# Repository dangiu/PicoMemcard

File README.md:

# PicoMemcard++

PicoMemcard++ lets you build a supercharged PlayStation memory card that can connect to your computer via USB, allowing you to transfer save files directly to and from your PSX. It can also be used to repurpose broken or counterfeit memory cards, turning them into something far more capable using only an RP2040. This project is a fork of the original work by [Dangiu].

When I decided to get involved, the original repository was read-only and no longer actively developed. I had a few simple goals in mind:
* There are many very cheap RP2040-based boards with built-in QSPI flash (up to 16MB), which can hold up to 128 virtual PSX memory card images.
* The project had been split into two versions: PicoMemcard (stuck at version 1.0) and PicoMemcard+ (which depends on a microSD card). I thought it made sense to merge them so both could benefit from ongoing updates.
* That’s when my journey with the project began.

## Features
* Able to faithfully simulate PSX Memory Card
* USB connection to import/export saves
* Allows to copy saves to/from any other memory card (using original PSX file manager)
* Allows to play burned CDs (thanks to [FreePSXBoot])
* Cheaper than an original memory card
* Can store hudreds of memory card images

## PicoMemcard++ vs PicoMemcard+/PicoMemcard
Because some features can’t be implemented using only a Pico/RP2040-Zero and require additional hardware, the original project was split into two versions:

* PicoMemcard was inspired by this project and aims to be the simplest and easiest version to build. It only requires a Raspberry Pi Pico, RP2040-Zero, or RP2040-Pro Micro. The original version supported only a single virtual memory card.
* PicoMemcard+ adds support for extra features, such as multiple memory card images, by using an additional SD card. However, this version also requires extra hardware, specifically a MicroSD SPI expansion board.
* **PicoMemcard++** (this fork) brings some of the features from PicoMemcard+ to the original PicoMemcard design, allowing users to switch between different memory cards without needing additional storage hardware. It’s a lower-cost option that combines ideas from both designs.

This approach was chosen because many users want the cheapest possible solution and don’t care about extra features. Others, however, are willing to spend a bit more to gain additional functionality.

Please note that the current release of PicoMemcard++ (when used without an SD card) comes with some limitations:
* Non-transparent write-back: during the synchronization process used to save new data, the memory card may briefly appear to disconnect.
* The connection to the PC (used to transfer save files from PSX games) is not fully plug-and-play. In some cases, you may need to reconnect the device.

## Bill of materials
* ** RP2040 Pico/Zero/Pro Micro** (around 2-3€).
* One of:
    * Custom [PicoMemcard PCB](#picomemcard-pcb)
    * Broken/Counterfeit/Original PSX Memory Card (counterfeit ones can be found on AliExpress for around 2-3€)
    * PSX/PS2 Controller Cable
    * CAT5 network cable and a bit of creativity.

Basically anything that will allow you to interface with the memory card slot pins will do. If you have a broken contoller you can cut off the cable and use that since controllers and memory cards share the same bus. Of course, plugging your memory card into the controller slot will prevent you from using 2 controllers at the same time.

[This guy] assembled one using a 3d-printed plastic shell and simple CAT5 network cable. I belive this is the cheapest method anybody has come up with until now.

In total building a PicoMemcard wil cost you less than buying a used original Memory Card!

## Video

## DIY

Getting your hands dirty, we will explore two different routes:
    * Custom [PicoMemcard PCB](#picomemcard-pcb)
    * [PSX Memory Card] (#picomemcard++-using-memory-card)

### PicoMemcard PCB

These are the custom PCBs designed and manufactured specifically for this application. They are not strictly required but make it much easier to build PicoMemcard since you don't need to cut up another memory card and all the soldering pads are easily accessible. All you need to do is to solder the Pico/RP2040-Zero on top of the PCB using a soldering iron.

The Raspberry Pi Pico or RP2040-Zero must sit flush on top of the PCB, fortunately both the Pico and RP2040-Zero provide castellated holes that are easy to solder directly to the PCB's pads. You can use some electrical tape to hold the board in place while you solder the first pins.

I've created a new version of the original PCBs the major difference are:
* The general size is smaller
* A new micro SD card module is supported. This module is smaller, easier to solder and should solve some of the power related issues that were previously present
* Is fitted for the installation of phisical switches used to switch memory card when PicoMemcard+ is used in systems that do not support switching via controller input (e.g. all PS2 models).

The KiCad and Gerber files are available in the repository. If you want to support the project you can request a PCB [from here]. 
Keep in mind that with the PS2 support release that will eventually happen the PCB may undergo some additional changes before its design is finalized.

### PicoMemcard++ using Memory Card
Raspberry Pi Pico, Pro Micro or RP2040-Zero require different pin usage for full compatibility.

The wiring diagrams below show how to build PicoMemcard by wiring respectively a Pico and an RP2040-Zero to a counterfeit memory card. For the other cases (wiring directly to the PSX or using a controller cable) the pins on Pico and RP2040-Zero are the same, the pinout of the PSX/controller can be found on [psx-spx]. The images show the bottom side of the memory card with the cover removed.

The dashed line on the PCB of the memory card is where you should cut a groove deep enough to disconnect the original circuitry from the traces. The yellow squares above the line indicate where you should scrape away the protective film in order to expose the copper traces and solder the wires onto them.

Finally the area at the bottom of the memory card is where you can cut a hole to feed the wires through connecting them to the Pico.
If you are using an RP2040-Zero you can also cut away part of the original Memory Card circuitry to fit it inside the original shell.

The connections in the PicoMemcard+ area are optional (using the optional MicroSD expansion board). Also remember to connect both ground and power to your SD card module (see [MicroSD Module](#microsd-module-for-picomemcard) section for more information).

#### PicoMemcard++ using a CounterFeit Memory Card without microSD module

In this subsection, I’ll show how to build a very simple version of the device without using an external microSD card. Since I don’t own a 3D printer, I used a counterfeit PSX memory card shell instead. The process involves the following steps:
1. Buy a memory card and unscrew the case:

2. Extract the PCB and desolder the internal components

3. Solder the RP2040-based board to the PCB

4. Enjoy the final result.

### MicroSD Module
There are many variations of MicroSD expansion boards with different pinouts and interfaces. The only requirement for PicoMemcard++ is that the module must provide an SPI interface. SPI interfaces have at least the following pins:
* Chip Select (CS) (sometime also called Slave Select (SS)).
* Clock (SCK or CLK).
* Master Output Slave Input (MISO).
* Master Input Slave Output (MOSI).

In addition you will need to connect power and ground to your module, some modules are design to work with 5V others with 3.3V (or both), luckily for us both voltages are available on Pico and RP2040-Zero as shown in the schematic in the section [above](#picomemcard-using-memory-card). Some module provides additional pins that can be left disconnected.

The new versions of the PCB are designed to use small modules such as this one:

This is mainly due to the following reasons:
* It comes withouth pre-soldered headers which makes it easier to solder onto the PicoMemcard PCB.
* Its smaller form factor allows for more flexibility.
* It should have less power issue than prevously used modules.

A good source for these modules is Aliexpress, in general you can search for `MicroSD SPI Expansion Board` and buy the cheapest one you find.

## Installation
1. Download the latest [release] for your board (Raspberry Pi Pico and RP2040-Zero require different binaries).
2. While pressing the 'BOOTSEL' or 'BOOT' button on your board, plug it into your computer. 
3. Drag and drop the PicoMemcard release onto your Raspberry Pi Pico.
4. PicoMemcard should appear on your PC as a USB drive.
5. Upload a memory card image to your PicoMemcard.

## Transfering Data
Memory card images must be exactly 128KB (131072 bytes) in size. PicoMemcard++ only supports files with `.MCR` extensions. However, `.MCR` and `.MCD` extensions are interchangable and can be converted to one another simply via renaming.
For other file formats, try using [MemcardRex] for converting to the desired output.

* **PicoMemcard** only supports a single image which must be named exactly `MEMCARD.MCR`.
* **PicoMemcard+** supports hundreds of images. Each image must be named `N.MCR` where `N` is an integer number (e.g. `0.MCR`, `1.MCR`...). On boot your previously loaded image will be reloaded, unless it's a fresh card then `0.MCR` will be loaded.
* **PicoMemcard++** supports up to 10 memory card images. As before, the naming convention is `N.MCR`, where `N` is an integer number (e.g. `0.MCR`, `1.MCR`...). n systems with 16MB of flash memory — such as some boards like the RP2040-Pro Micro — the limit is increased to 100 images.

Inside `docs/images` you can find two memory card images. One has a couple of saves on it so you can test if everything works correctly, the other is completely empty.

## Switching/Creating Images
On **PicoMemcard+** you can switch the active memory card image with the following inputs:
* `L1 + L2 + R1 + R2 + DPAD UP` will switch to the next image (e.g from `1.MCR` to `2.MCR`).
* `L1 + L2 + R1 + R2 + DPAD DOWN` will switch to the previous image (e.g from `1.MCR` to `0.MCR`).

Additionally you can create a new empty memory card image (and automatically switch to it) by pressing  `L1 + L2 + R1 + R2 + TRIANGLE`.

**Attention**: this method only works on PSX if the controller used to provide the input is plugged in the same slot as PicoMemcard (exactly under it). Using a controller from a different slot will have no effect.

Additionally this method does not work on PS2 Memory Cards and Controllers are wired on a different bus.

## Syncing Changes
Generally speaking, new data written to PicoMemcard (e.g. when you save) is permanently stored only after a short period of time (due to hardware limitation). The on board LED indicates whether all changes have been stored or not, in particular:
* On RP2040 Pico/Pro Micro the LED will be on when all changes have been saved, off otherwise.
* On RP2040-Zero the LED will be solid when all changes have been saved, red otherwise.

Unlike **PicoMemcard+** that tries to write new changes as soon as possible, **PicoMemcard++** will generally do it only after a period of inactivity (around 5 seconds).

**Attention**: after you save your game, make sure to wait for the LED to be solid before turning off the console otherwise you might lose your more recent progress!

## 3D-Printed Case
I've finally designed a 3D-printable case for the different PicoMemcard PCBs. It helps inserting correctly the PCB and ensuring that the the connection to the PSX is optimal. The same result, albeit more janky, can be achieved using a folded sheet of paper as a spacer.

The cases are designed following a minimalistic approach, they consist of a single piece which holds tightly the PCB using very small clips without requiring any additional hardware. To assemble it, simply slide in the PCB from the back of the case (opposite to the side connecting to the PSX). Cases for the fullsize PCB are designed to support the MicroSD expansion module.

Here is the download for the STL files:
* [Design by DanGiu](https://www.thingiverse.com/thing:5488778)

If you don't like this case you can check out other designs many people have already created! I've not tested them personally but here they are:
* [Design by brik1111](https://www.thingiverse.com/thing:5453156)
* [Design by bbsan2k](https://www.thingiverse.com/thing:5460187)

## Troubleshooting and LED Indicator
Generally speaking the onboard LED will provide a pretty good indication regarding the status of PicoMemcard.

In particular, the RP2040-Zero has RGB LED that provides a more clear output. The Pico on the other hand as only a green LED and different blinking patterns indicate different statuses.

### PicoMemcard++ Status
| Status | Pico | RP2040-Zero
| --- | --- | --- |
| Failed to read SD card | Blinking led  | Red blinking led
| Data not fully synced (do not turn off PSX)| Led off | Red led (or flashing red) |
| Data synced | Led on | Solid led |
| Memory Card image changed | Three fast blinks | Single blue blink |
| Memory Card image not changed (end of list) | Nine fast blinks | Single orange blink |
| New Memory Card image created | Multiple very fast blinks | Single light blue blink |

## General Warnings
I would recommend to never plug PicoMemcard both into the PC (via USB) and the PSX at the same time! Otherwise the 5V provided by USB would end up on the 3.3V rail of the PSX. I'm not really sure if this could cause actual damage but I would avoid risking it.

If you really need to have the Pico plugged into both the USB and PSX (e.g. for debugging purposes), disconnect the 3.3V line from the VBUS pin. In this way you can power on the Pico using a simple USB phone charger or by plugging it into your PC.

As a disclamer, I don't take any responsability for what will happen to your console when using PicoMemcard/PicoMemcard+.

## Project Updates
### 16 may 2026
A fork of the original project that revives and merges previously abandoned features, along with updated documentation and support for additional boards and functionalities.

### 5 February 2023
Sorry everybody but I've been quite inactive on the project lately. Due to a change of job IRL I have less time to work for the moment.
Anyway, behind the scenes I've been trying to add support for PS2 memory card but I'm afraid that will require the addition of an extra hardware component unless I am able to develop an efficient cacheing mechanisms or something similar. Anyway I'll keep working on it when I have free time. I have in mind many improvement for the project and I think the future of it is going to be exciting.

Special thanks to everybody that supported it so far! You are all amazing.

## Design
For people interested in understanding how PicoMemcard works I provide a more extensive explanation in [this post] (although now somewhat outdated).

## Thanks To
* [psx-spx] and Martin "NO$PSX" Korth - PlayStation Specifications and documented Memory Card protocol and filesystem.
* [Andrew J. McCubbin] - Additional information about Memory Card and Controller communication with PSX.
* [littlefs] - Filesystem designed to work on NOR flash used by many microcontrollers, including the Raspberry Pi Pico.
* [ChaN FatFS] - FAT filesystem implementation for embedded devices.
* [Scoppy] - Use your Raspberry Pi Pico as an oscilloscope, very cheap and accurate. Without this I would have not been able to debug many issues.
* [PulseView] - Used to import, visualize and manipulate the data from Scoppy on a PC.

[Dangiu]: https://github.com/dangiu/PicoMemcard
[FreePSXBoot]: https://github.com/brad-lin/FreePSXBoot
[psx-spx]: https://psx-spx.consoledev.net/pinouts/#controller-ports-and-memory-card-ports
[Andrew J. McCubbin]: http://www.emudocs.org/PlayStation/psxcont/
[littlefs]: https://github.com/littlefs-project/littlefs
[ChaN FatFS]: http://elm-chan.org/fsw/ff/00index_e.html
[Scoppy]: https://github.com/fhdm-dev/scoppy
[PulseView]: https://sigrok.org/wiki/PulseView
[release]: https://github.com/dangiu/PicoMemcard/releases/latest
[this post]: https://dangiu.github.io/2022/05/13/picomemcard.html
[from here]: https://forms.gle/f6XHtz6W5fn5qDZV7
[This guy]: https://github.com/MrSVCD/PicoPSX_3D
[MemcardRex]: https://github.com/ShendoXT/memcardrex

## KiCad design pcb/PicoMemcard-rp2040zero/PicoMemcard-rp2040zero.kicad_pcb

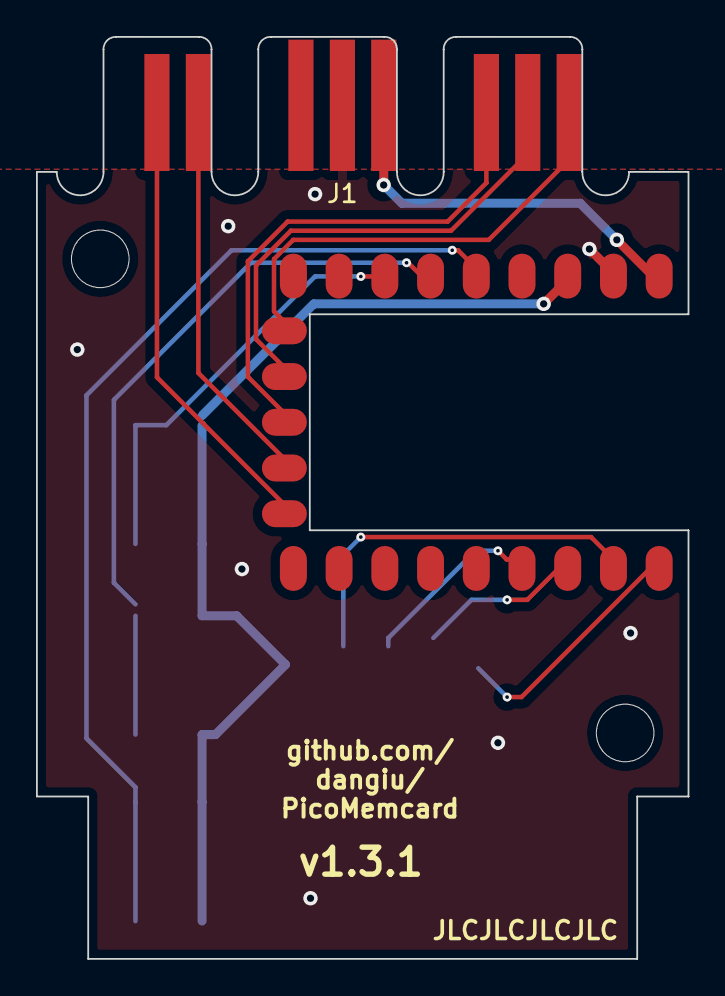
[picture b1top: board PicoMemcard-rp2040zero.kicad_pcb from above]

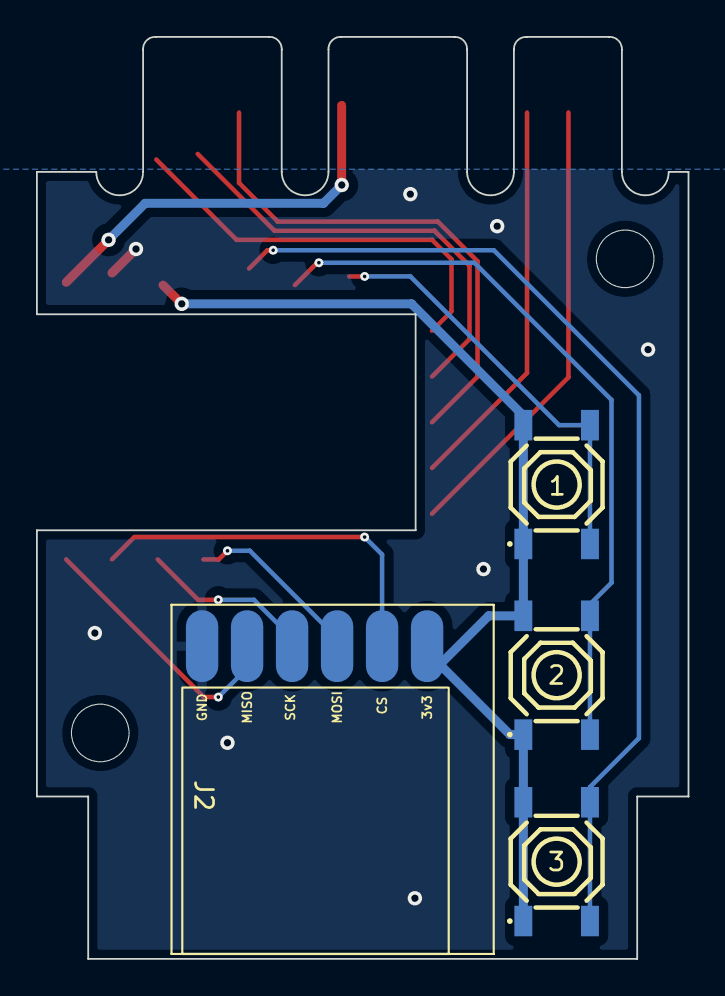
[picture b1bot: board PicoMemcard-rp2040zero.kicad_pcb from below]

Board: 2 copper layers, 36.2 x 51.2 mm, 8 parts (4 on the bottom side), 15 nets.

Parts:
1, 2, 3: TS-1187A-B-A-B; SW-SMD_4P-L5.1-W5.1-P3.70-LS6.5-TL-2
H1, H2: M3; MountingHole_3.2mm_M3
J1: PSX Memory Card Interface; MemoryCardConnector
J2: MicroSD SPI; MicroSD_SPI_small
U1: rp2040-zero; rp2040-zero-smd

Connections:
+3V3: 1.1 (A), 1.2 (B), 2.1 (A), 2.2 (B), 3.1 (A), 3.2 (B), J2.1, U1.21 (3V3)
+5V: J1.5 (5V), U1.23 (5V)
ACK: J1.8 (ACK), U1.14 (13)
CLK: J1.7 (CLK), U1.13 (12)
CMD: J1.2 (CMD), U1.11 (10)
CS: J2.2, U1.2 (1)
DAT: J1.1 (DAT), U1.10 (9)
GND: J1.4 (GND), J2.6, U1.22 (GND)
GP26: 1.3 (C), 1.4 (D), U1.17 (26)
GP27: 2.3 (C), 2.4 (D), U1.18 (27)
GP28: 3.3 (C), 3.4 (D), U1.19 (28)
MISO: J2.5, U1.1 (0)
MOSI: J2.3, U1.4 (3)
SCK: J2.4, U1.3 (2)
SEL: J1.6 (SEL), U1.12 (11)

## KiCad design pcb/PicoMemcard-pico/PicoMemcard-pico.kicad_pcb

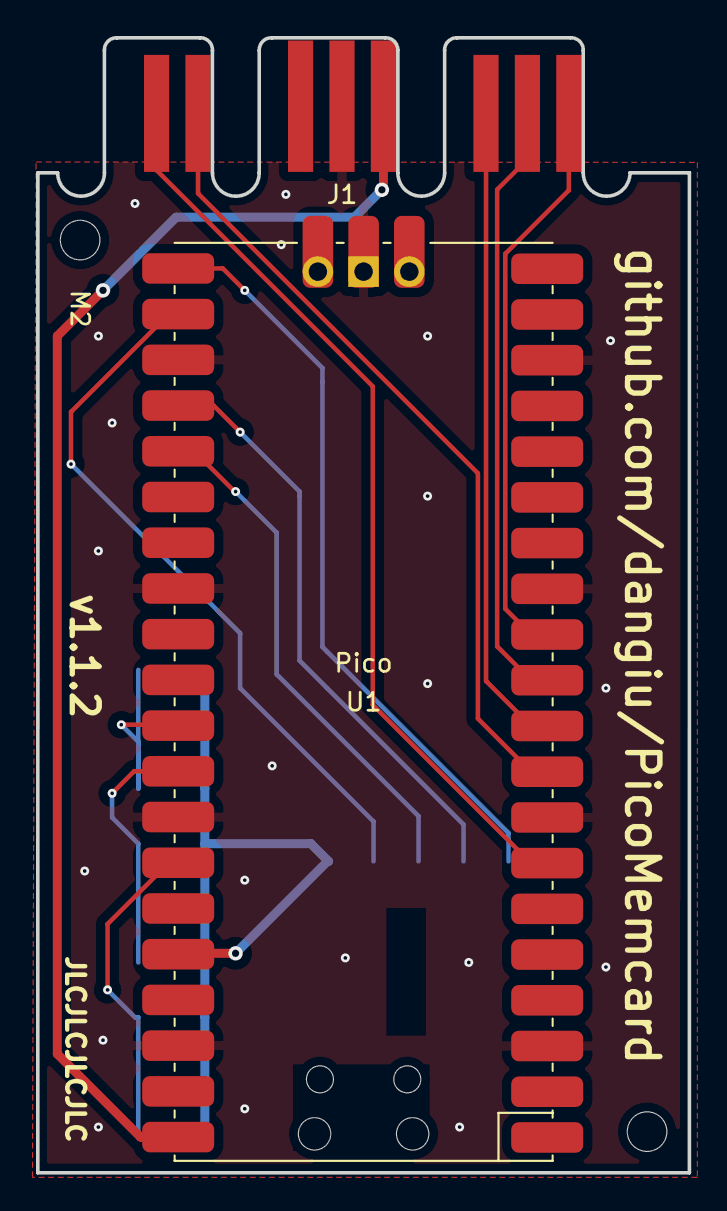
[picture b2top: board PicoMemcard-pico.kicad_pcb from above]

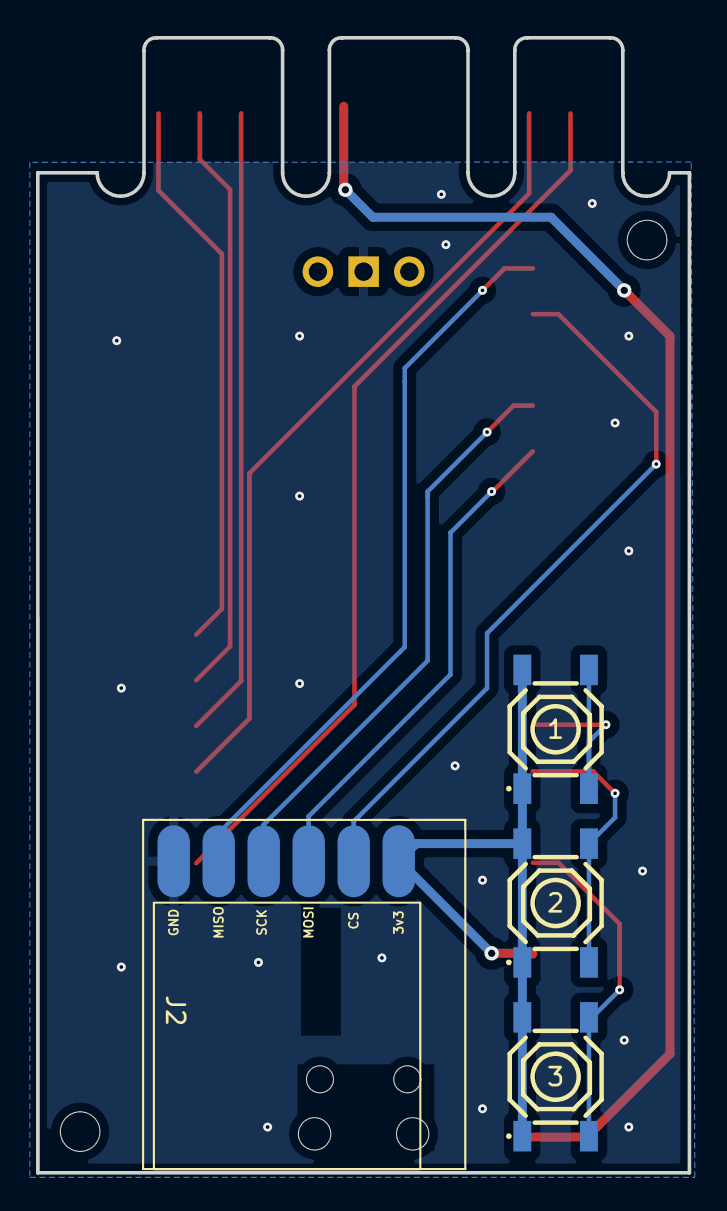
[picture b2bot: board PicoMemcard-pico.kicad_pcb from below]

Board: 2 copper layers, 36.2 x 63.1 mm, 8 parts (4 on the bottom side), 15 nets.

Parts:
1, 2, 3: TS-1187A-B-A-B; SW-SMD_4P-L5.1-W5.1-P3.70-LS6.5-TL-2
J1: PSX Memory Card Interface; MemoryCardConnector
J2: microSD_SPI_small; MicroSD_SPI_small
M2, M2#2: MountingHole; MountingHole_2.2mm_M2_DIN965
U1: Pico; RPi_Pico_SMD_TH

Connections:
+3V3: 1.1 (A), 1.2 (B), 2.1 (A), 2.2 (B), 3.1 (A), 3.2 (B), J2.1, U1.36 (3V3)
+5V: J1.5 (3.3V), U1.40 (VBUS)
ACK: J1.8 (ACK), U1.12 (GPIO9)
CLK: J1.7 (CLK), U1.11 (GPIO8)
CMD: J1.2 (CMD), U1.9 (GPIO6)
CS: J2.2, U1.22 (GPIO17)
DAT: J1.1 (DAT), U1.7 (GPIO5)
GND: J1.4 (GND), J2.6, U1.3 (GND), U1.8 (GND), U1.13 (GND), U1.18 (GND), U1.23 (GND), U1.28 (GND), U1.33 (AGND), U1.38 (GND), U1.42 (GND)
GP26: 1.3 (C), 1.4 (D), U1.31 (GPIO26_ADC0)
GP27: 2.3 (C), 2.4 (D), U1.32 (GPIO27_ADC1)
GP28: 3.3 (C), 3.4 (D), U1.34 (GPIO28_ADC2)
MISO: J2.5, U1.21 (GPIO16)
MOSI: J2.3, U1.25 (GPIO19)
SCK: J2.4, U1.24 (GPIO18)
SEL: J1.6 (SEL), U1.10 (GPIO7)

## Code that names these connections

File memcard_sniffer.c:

/**
 * @file protocol_sniffer.c
 * @author Daniele Giuliani (danielegiuliani0@gmail.com)
 * @brief Utility used to sniff PSX SPI protocol (CMD and DAT lines)
 * @version 0.1
 * @date 2022-04-08
 */

#include <stdio.h>
#include "pico/stdlib.h"
#include "hardware/pio.h"
#include "hardware/irq.h"
#include "psxSPI.pio.h"

#define PIN_DAT 5
#define PIN_CMD 6
#define PIN_SEL 7
#define PIN_CLK 8
#define PIN_ACK 9

#define BUFF_LEN 4096

PIO pio = pio0;

uint smSelMonitor;
uint smCmdReader;
uint smDatReader;

uint offsetSelMonitor;
uint offsetCmdReader;
uint offsetDatReader;

uint32_t buffIndex = 0;
uint8_t cmdBuffer[BUFF_LEN];
uint8_t datBuffer[BUFF_LEN];

bool restartProto = false;

/**
 * @brief Interrupt handler called when SEL goes high
 * Resets cmdReader and datWriter state machines
 */
void pio0_irq0() {
	pio_set_sm_mask_enabled(pio, 1 << smCmdReader | 1 << smDatReader, false);
	pio_restart_sm_mask(pio, 1 << smCmdReader | 1 << smDatReader);
	pio_sm_exec(pio, smCmdReader, pio_encode_jmp(offsetCmdReader));	// restart smCmdReader PC
	pio_sm_exec(pio, smDatReader, pio_encode_jmp(offsetDatReader));	// restart smDatReader PC
	pio_interrupt_clear(pio0, 0);
	pio_enable_sm_mask_in_sync(pio, 1 << smCmdReader | 1 << smDatReader);
	restartProto = true;
}

int main() {
	stdio_init_all();

	printf("\n\nBeginning Execution...\n");

	/* Setup PIO interrupts */
	irq_set_exclusive_handler(PIO0_IRQ_0, pio0_irq0);
	irq_set_enabled(PIO0_IRQ_0, true);

	offsetSelMonitor = pio_add_program(pio, &sel_monitor_program);
	offsetCmdReader = pio_add_program(pio, &cmd_reader_program);
	offsetDatReader = pio_add_program(pio, &dat_reader_program);

	smSelMonitor = pio_claim_unused_sm(pio, true);
	smCmdReader = pio_claim_unused_sm(pio, true);
	smDatReader = pio_claim_unused_sm(pio, true);

	dat_reader_program_init(pio, smDatReader, offsetDatReader, PIN_DAT);
	cmd_reader_program_init(pio, smCmdReader, offsetCmdReader, PIN_CMD);
	sel_monitor_program_init(pio, smSelMonitor, offsetSelMonitor, PIN_SEL);

	/* Enable all SM simultaneously */
	uint32_t smMask = (1 << smSelMonitor) | (1 << smCmdReader) | (1 << smDatReader);
	pio_enable_sm_mask_in_sync(pio, smMask);

	/* Samping phase */
	for(int i = 0; i < BUFF_LEN; ++i) {
		cmdBuffer[index] = read_byte_blocking(pio, smCmdReader);
		datBuffer[index] = read_byte_blocking(pio, smDatReader);
	}

	/* Printing results */
	for(int i = 0; i < BUFF_LEN; ++i) {
		printf("\t%.2x\t%.2x\n", cmdBuffer[i], datBuffer[i]);
	}
}

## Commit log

2022-04-05 Add initial .gitignore and IDE configuration
2022-04-05 Initial testing of custom SPI, able to read correctly CMD, unable to answer using DAT and ACK
2022-04-08 Update IDE configuration, add PIO sm supporting modified psx spi, add showcase of joypad toggle
2022-04-08 Refractor comments, code clean-up
2022-04-26 First working version of memcard simulation
2022-05-02 Implement ID command handling, code and comments cleanup
2022-05-02 Add memory card status response code
2022-05-02 Move to picoprobe for debugging
2022-05-02 Update memcard sniffer utility, add freepsxboot raw image
2022-05-10 First working version with MSC, memcard simulation and sync
2022-05-10 Remove unused submodule
2022-05-10 Update VSCode configuratioN
2022-05-10 Update memcard sync mechanism
2022-05-10 Add FatFS library
2022-05-10 Remove obsolete dependencies
2022-05-14 Update CMake and launch configuration, add led status indicator to memcard simulation mode
2022-05-14 Add README and documentation
2022-05-16 Add memory card images
2022-05-16 Add release
2022-05-23 Enlarge virtual FAT disk to accomodate Windows Storage Service data preventing user from transfering memory card image on first installation
2022-06-05 Update README.md, add Custom PCB section
2022-06-06 Fix some README typos/grammar
2022-06-09 Remove placeholder MEMCARD.MCR creation, fixes #3
2022-06-10 Added SD card mount error check.
2022-06-10 Remove developer/environment specific C/C++ vscode plugin settings.
2022-06-10 Initial SD card support.
2022-06-10 More accurate acks
2022-06-10 Memcard simulation on separate thread
2022-06-15 Initial work on stateful memory card simulation
2022-06-15 Rewrite memcard simulator as a state machine. Now more closely matches the behaviour of an official memory card.
2022-06-15 More work on state machine
2022-06-25 Correct mistakes and add gitignore entries for clion.
2022-07-02 Initial ps2 compatability work.
2022-07-02 Initial work on queue-based syncing
2022-07-09 Concurrency fixes
2022-07-09 Fix page sync size.
2022-07-09 Stateful MC simulation
2022-07-09 SD card functionality
2022-07-09 Address changes and debugging
2022-07-10 Add sector log and fix issue where the syncing process was treating the sector number as an absolute address.
2022-07-11 Initial bank switching work.
2022-07-11 Banked syncing
2022-07-11 Display the specific FS error using LED blink codes
2022-07-12 OLED Driver, splash screen and bank display.
2022-07-13 Bank switching
2022-07-13 Fix clion automatic cmake updates.
2022-07-13 Remove reserved space for LittleFS no longer needed in PMC+
2022-07-31 Code refractoring, bugfixing and new features: - update .gitignore - update psxPSI code - changed simulation to state maching based (following darren approach) - add missing NULL checks in memory_car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
    Compilation requires fix for pico-sdk not yet merged:
    https://github.com/raspberrypi/pico-sdk/pull/936
2022-07-31 Add support for RP2040-zero LED
2022-07-31 Remove 0 byte MEMCARD.MCR from virtual RAM disk
2022-07-31 Add manual sync option, require reworking PIO code
2022-08-01 Code refractoring & reimplementation of USB functionality - reworked memory_card (initialization, null check, error codes, type and more) - reintroduced MSC capabilities (previosly removed) - reduced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
2022-08-01 Add missing config include
2022-08-01 Reworked queue sync: cleaner faster and less memory used, add sync status led
2022-08-01 Remove obsolete comment
2022-08-02 Add multiple memory card image support, with controller input for switching
2022-08-02 Add SD pinout to global configuration, fix RP2040-Zero SD pinouts
2022-08-02 Fix image not appearing in README.md
2022-08-17 Add support for Adafruit QTPY RP2040, move some code around to better support multiple boards
2022-08-25 Rework image switching to lookup explicitely filesystem instead of using blind index, fixes #16
2022-08-26 Add controller input (STRT+SEL+TRNGL) to create new empty memory card image and switch to it, closes #21
2022-08-31 Fix WS2812 LED passing data on DO instead of interpreting it, update color scheme
2022-08-31 Update README.md, add MicroSD section and new features
2022-09-09 Update README.md with latest video release
2023-02-03 PicoMemCard+ now reloads the last card you had loaded after a restart.
    Handles creating new cards, index being out of range and the dat file not existing.
    Changed out of sync state LED to red, as orange looks very similar to green on RP2040 Zero.
    Added small delay to out of sync state LED as previously it would flash green and red/orange quickly and would be hard to see if it is still syncing. Note: This doesn't add any noticeable delay to sa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
    Added flag to invert red and green for newer RP2040 Zero boards.
2023-02-03 Changed out of sync state LED to red, as orange looks very similar to green on RP2040 Zero. Added small delay to out of sync state LED as previously it would flash green and red/orange quickly and wo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
2023-02-05 Update README, add KiCad and Gerber for new PCB
2023-03-09 Submodules using https do not require publickey
2023-03-09 PICO_DEFAULT_LED_PIN is already defined in pico.h
2023-03-09 Pico_W LED Support
2023-03-09 CYW43_WL_GPIO_LED_PIN already defined in pico_w.h
2023-03-16 Fixed bug caused by find/replace
2023-03-19 fixes dangiu/PicoMemcard/issues/48
2023-03-19 Simplifies dangiu/PicoMemcard#48
2023-03-19 Fixes dangiu/PicoMemcard#49
2023-03-19 Simplifies dangiu/PicoMemcard#49
2023-03-19 Add ability to receive GameID
2023-03-19 New creation method, Fixes dangiu/PicoMemcard#40
2023-03-19 memcard_n is now defined
2023-05-12 Update README, add KiCad and Gerber for new PCB
    (cherry picked from commit b31d37a9591b99b14c3917d8c4e2e22f61f843ec)
2023-05-12 Add improved PIO code, add improved interrupt and ack handling, general code cleanup
2023-05-12 Refractor code, improved queue and transition handling, switch from sm approach to linear one
2023-06-03 Fix pio code, improve output
2023-06-03 Fix bad function definition when compiling for RP2040-Zero
2023-10-01 RGB LED for Aliexpress PicoMemcard
2023-10-01 Update README.md with Pico RGB colors
2023-11-12 refactor: updated pio related code, no sel_monitor sm needed anymnore
2023-11-12 fix: remove useless delay
2024-01-31 Update config.h
    attempt to make compatible with RP2040-LCD-.0.96 to show status or at least colors to make sure it is loaded and functioning properly
2024-02-02 needed for LCD
2024-02-02 Needed for LC
2024-02-02 Prelim 0in96 LCD Support
2024-02-02 More LCD stuff
2024-02-02 Update CMakeLists.txt
    Adding files for LCD to cmake
2024-02-02 Update CMakeLists.txt
    oops forgot part of a line
2024-02-02 Update CMakeLists.txt
    needed to fix compiler errors
2024-02-02 Update main.c
    maybe get output from lcd
